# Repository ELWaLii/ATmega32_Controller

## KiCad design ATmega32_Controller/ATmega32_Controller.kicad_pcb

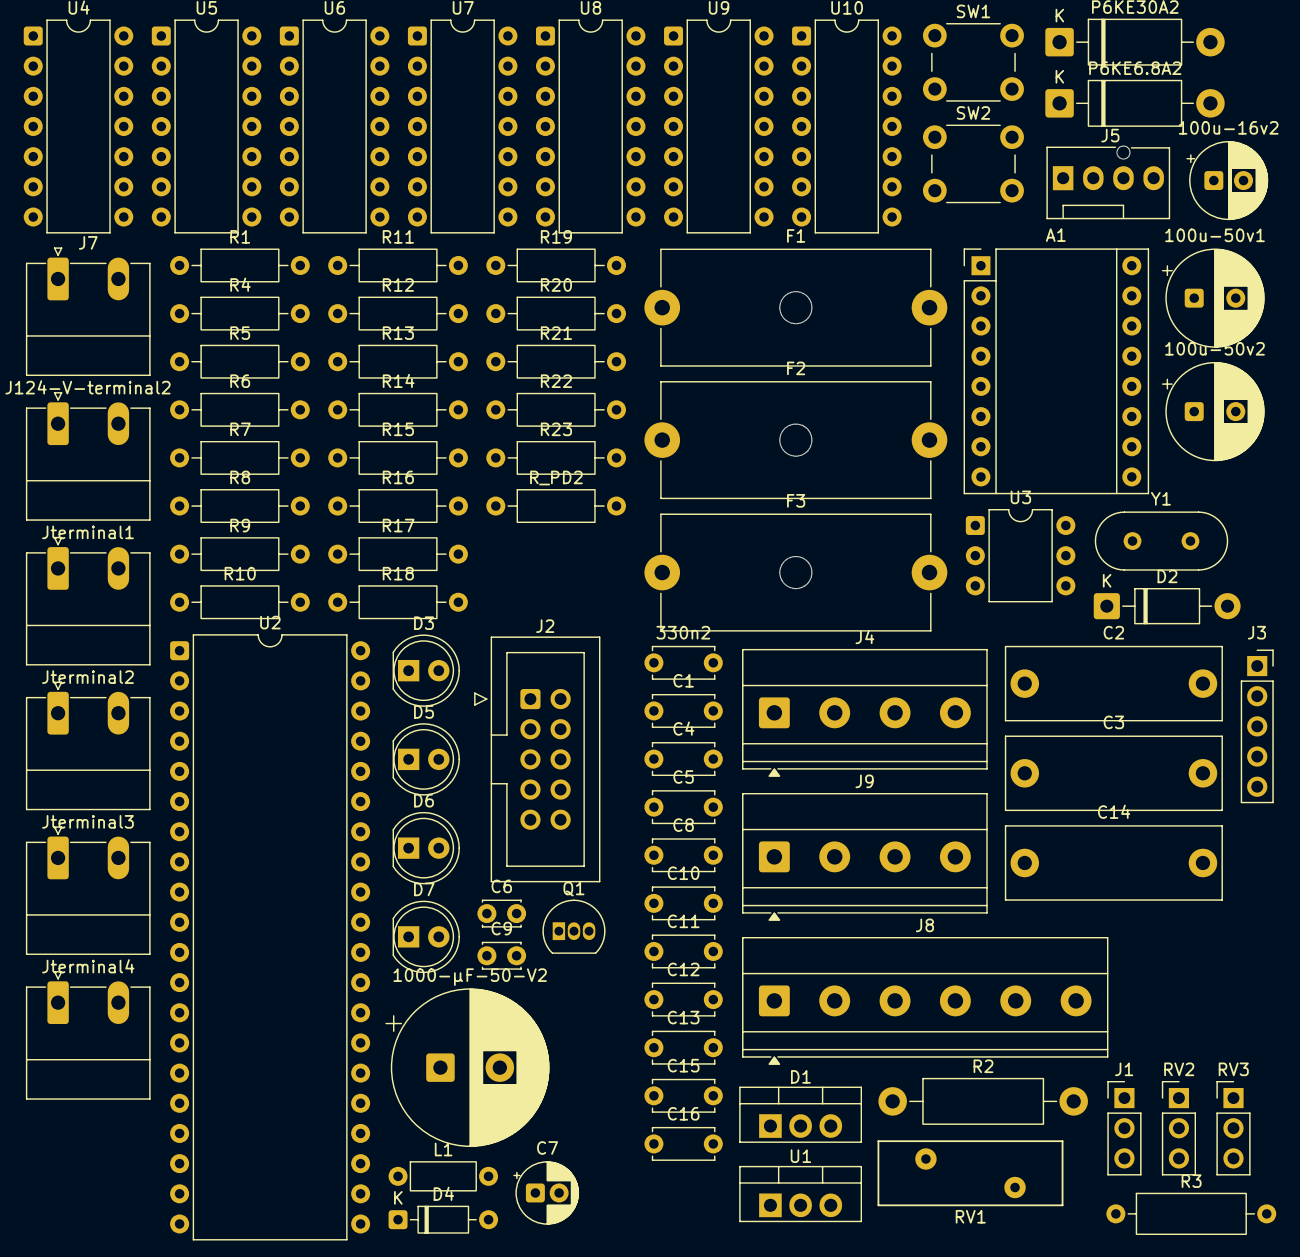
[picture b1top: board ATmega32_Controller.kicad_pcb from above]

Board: 2 copper layers, 89 parts (0 on the bottom side), 59 nets, no tracks yet.

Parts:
100u-16v2: C_Polarized; CP_Radial_D6.3mm_P2.50mm
100u-50v1, 100u-50v2: C_Polarized; CP_Radial_D8.0mm_P3.50mm
330n2: C; C_Disc_D5.0mm_W2.5mm_P5.00mm
1000-µF-50-V2: C_Polarized; CP_Radial_D13.0mm_P5.00mm
A1: Pololu_Breakout_DRV8825; Pololu_Breakout-16_15.2x20.3mm
C1, C4, C5, C8, C10, C11, C15, C16: 100nf; C_Disc_D5.0mm_W2.5mm_P5.00mm
C2, C3, C14: 100nf; C_Rect_L18.0mm_W6.0mm_P15.00mm_FKS3_FKP3
C6, C9: 22pf; C_Disc_D3.0mm_W2.0mm_P2.50mm
C7: 10uf 16v; CP_Radial_D5.0mm_P2.00mm
C12, C13: 1nf; C_Disc_D5.0mm_W2.5mm_P5.00mm
D1: BTA16; TO-220-3_Vertical
D2: 1N4007; D_DO-41_SOD81_P10.16mm_Horizontal
D3: power_Led; LED_D5.0mm
D4: 1N4148; D_DO-35_SOD27_P7.62mm_Horizontal
D5: ALARM; LED_D5.0mm
D6: HEAT; LED_D5.0mm
D7: MOTOR; LED_D5.0mm
F1: Fuse; Fuseholder_Cylinder-5x20mm_Schurter_0031_8201_Horizontal_Op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
F2: HTR; Fuseholder_Cylinder-5x20mm_Schurter_0031_8201_Horizontal_Op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
F3: PSU; Fuseholder_Cylinder-5x20mm_Schurter_0031_8201_Horizontal_Op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
J1: UART CONN; PinHeader_1x03_P2.54mm_Vertical
J2: AVR-ISP-10; IDC-Header_2x05_P2.54mm_Vertical
J3: MAX6675 module socket; PinSocket_1x05_P2.54mm_Vertical
J4: J_ENC; TerminalBlock_Phoenix_MKDS-1,5-4-5.08_1x04_P5.08mm_Horizont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
J5: LCD I2C header; FanPinHeader_1x04_P2.54mm_Vertical
J7: J_VMOT; PhoenixContact_MC_1,5_2-G-5.08_1x02_P5.08mm_Horizontal
J8: J_DRV; TerminalBlock_Phoenix_MKDS-1,5-6-5.08_1x06_P5.08mm_Horizont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
J9: MotorTerminal; TerminalBlock_Phoenix_MKDS-1,5-4-5.08_1x04_P5.08mm_Horizont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
J124-V-terminal2: Screw_Terminal_01x02; PhoenixContact_MC_1,5_2-G-5.08_1x02_P5.08mm_Horizontal
Jterminal1: J_ESTOP; PhoenixContact_MC_1,5_2-G-5.08_1x02_P5.08mm_Horizontal
Jterminal2: J_PSU; PhoenixContact_MC_1,5_2-G-5.08_1x02_P5.08mm_Horizontal
Jterminal3: J_HTR; PhoenixContact_MC_1,5_2-G-5.08_1x02_P5.08mm_Horizontal
Jterminal4: J_AC; PhoenixContact_MC_1,5_2-G-5.08_1x02_P5.08mm_Horizontal
L1: 10uh; L_Axial_L5.3mm_D2.2mm_P7.62mm_Horizontal_Vishay_IM-1
P6KE6.8A2, P6KE30A2: D_TVS; D_DO-15_P12.70mm_Horizontal
Q1: BC337; TO-92_Inline
R1, R4: 10k; R_Axial_DIN0207_L6.3mm_D2.5mm_P10.16mm_Horizontal
R2: 100 1W; R_Axial_DIN0411_L9.9mm_D3.6mm_P15.24mm_Horizontal
R3: 360 \ 0.5 W; R_Axial_DIN0309_L9.0mm_D3.2mm_P12.70mm_Horizontal
R5, R9, R21, R22, R23: 1k; R_Axial_DIN0207_L6.3mm_D2.5mm_P10.16mm_Horizontal
R6: 180; R_Axial_DIN0207_L6.3mm_D2.5mm_P10.16mm_Horizontal
R7, R19, R20: 4.7K; R_Axial_DIN0207_L6.3mm_D2.5mm_P10.16mm_Horizontal
R8: 10K; R_Axial_DIN0207_L6.3mm_D2.5mm_P10.16mm_Horizontal
R10, R12, R13, R15, R17: 1K; R_Axial_DIN0207_L6.3mm_D2.5mm_P10.16mm_Horizontal
R11, R14: 2.2 k; R_Axial_DIN0207_L6.3mm_D2.5mm_P10.16mm_Horizontal
R16, R18: 1M; R_Axial_DIN0207_L6.3mm_D2.5mm_P10.16mm_Horizontal
RV1: 14D471K; RV_Disc_D15.5mm_W5.4mm_P7.5mm
RV2, RV3: 10 kΩ; PinHeader_1x03_P2.54mm_Vertical
R_PD2: 10K; R_Axial_DIN0207_L6.3mm_D2.5mm_P10.16mm_Horizontal
SW1: Reset; SW_PUSH_6mm
SW2: SW_Push; SW_PUSH_6mm
U1: L7805; TO-220-3_Vertical
U2: ATmega32-16P; DIP-40_W15.24mm
U3: MOC3041M; DIP-6_W7.62mm
U4, U5, U6, U7, U8, U9, U10: 74HC14; DIP-14_W7.62mm
Y1: Crystal; Crystal_HC49-U_Vertical

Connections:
+5V: 100u-16v2.1, A1.11 (M1), A1.13 (~RST), A1.14 (~SLP), C1.1, C5.1, C11.2, C14.1, D2.2 (A), D4.1 (K), J2.2 (VCC), J3.1, J4.1, J5.2, J8.1, J8.3, J8.5, Jterminal1.2, L1.1, P6KE6.8A2.1 (A1), R1.1, R4.2, R11.1, R14.1, R19.1, R20.1, R23.1, U1.3 (OUT), U2.10 (VCC), U10.14 (VCC)
+5VA: C7.1, C8.2, L1.2, RV2.1, RV3.1, U2.30 (AVCC)
+24V: 100u-50v1.1, 100u-50v2.1, 330n2.1, 1000-µF-50-V2.1, A1.8 (VMOT), D2.1 (K), F1.1, J7.1, P6KE30A2.1 (A1), U1.1 (IN)
ADC_SPD: C16.1, R17.2, R18.2, U2.39 (PA1)
ADC_TEMP: C15.1, R15.2, R16.2, U2.40 (PA0)
ATMEGA_RESET: C10.2, D4.2 (A), J2.5 (~RST), R1.2, SW1.2, U2.9 (~RESET)
A_F: C13.2, R12.2, U4.1
A_N: U4.2, U5.3
BTN_START: SW2.2, U2.24 (PC2)
B_F: C12.2, R13.2, U6.5
B_N: U6.6, U7.9
DIR: A1.16 (DIR), J8.4, U2.20 (PD6)
ENA: A1.9 (~EN), J8.6, U2.18 (PD4)
ENC_A: U2.16 (PD2), U5.4
ENC_A_RAW: J4.3, R12.1, R14.2
ENC_B: U2.17 (PD3), U7.8
ENC_B_RAW: J4.4, R11.2, R13.1
ESTOP_OK: R10.2, U2.3 (PB2)
GATE: R5.1, U3.4
GND: 100u-16v2.2, 100u-50v1.2, 100u-50v2.2, 330n2.2, 1000-µF-50-V2.2, A1.1 (GND), A1.7 (GND), A1.10 (M0), A1.12 (M2), C1.2, C4.1, C5.2, C6.2, C7.2, C8.1, C9.2, C10.1, C11.1, C12.1, C13.1, C14.2, C15.2, C16.2, D3.1 (K), D5.1 (K), D6.1 (K), D7.1 (K), J1.1, J2.4 (GND), J2.6 (GND), J2.8 (GND), J2.10 (GND), J3.2, J4.2, J5.1, J7.2, J124-V-terminal2.1, P6KE6.8A2.2 (A2), P6KE30A2.2 (A2), Q1.3 (E), R8.1, R16.1, R18.1, RV2.3, RV3.3, R_PD2.2, SW1.1, SW2.1, U1.2 (GND), U2.11 (GND), U2.31 (GND), U8.11, U9.13, U10.7 (GND)
HEATER_5V: Jterminal1.1, R6.1, R10.1, R_PD2.1
HEATER_CTRL: R7.1, U2.1 (PB0)
I2C_SCL: J5.4, R20.2, U2.22 (PC0)
I2C_SDA: J5.3, R19.2, U2.23 (PC1)
LED_ALARM: R9.1, U2.25 (PC3)
LED_HEAT: R21.1, U2.26 (PC4)
LED_MOTOR: R22.1, U2.27 (PC5)
L_HTR: F2.1, R2.1, R3.1
L_IN: C3.1, F2.2, F3.2, Jterminal4.2, RV1.1
L_PSU: F3.1, Jterminal2.2
L_SW: C2.2, Jterminal3.2, R5.2
MAX_CS: J3.4, R4.1, U2.5 (PB4)
MOC_P6: R3.2, U3.6
NAC: C3.2, Jterminal4.1, RV1.2
N_AC: Jterminal2.1, Jterminal3.1
unnamed: A1.4 (A1), J9.1
unnamed: A1.3 (A2), J9.2
unnamed: A1.5 (B1), J9.3
unnamed: A1.6 (B2), J9.4
unnamed: D3.2 (A), R23.2
unnamed: D5.2 (A), R9.2
unnamed: D6.2 (A), R21.2
unnamed: D7.2 (A), R22.2
unnamed: F1.2, J124-V-terminal2.2
unnamed: Q1.2 (B), R7.2, R8.2
unnamed: Q1.1 (C), U3.2
unnamed: R6.2, U3.1
unnamed: C4.2, U2.32 (AREF)
POT1_W: R15.1, RV2.2
POT2_W: R17.1, RV3.2
SNUB: C2.1, R2.2
SPI_MISO: J2.9 (MISO), J3.5, U2.7 (PB6)
SPI_MOSI: J2.1 (MOSI), U2.6 (PB5)
SPI_SCK: J2.7 (SCK), J3.3, U2.8 (PB7)
STEP: A1.15 (STEP), J8.2, U2.19 (PD5)
UART_RX: J1.3, U2.14 (PD0)
UART_TX: J1.2, U2.15 (PD1)
XTAL1: C9.1, U2.13 (XTAL1), Y1.2
XTAL2: C6.1, U2.12 (XTAL2), Y1.1
